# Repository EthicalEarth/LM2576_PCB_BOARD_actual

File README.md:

# LM2576_PCB_BOARD_actual
Good step-down converter. Project have stable status and released. After build, this board works perfectly from 2016-2021
Requires more space for radiators, but works great with forced ventilation.

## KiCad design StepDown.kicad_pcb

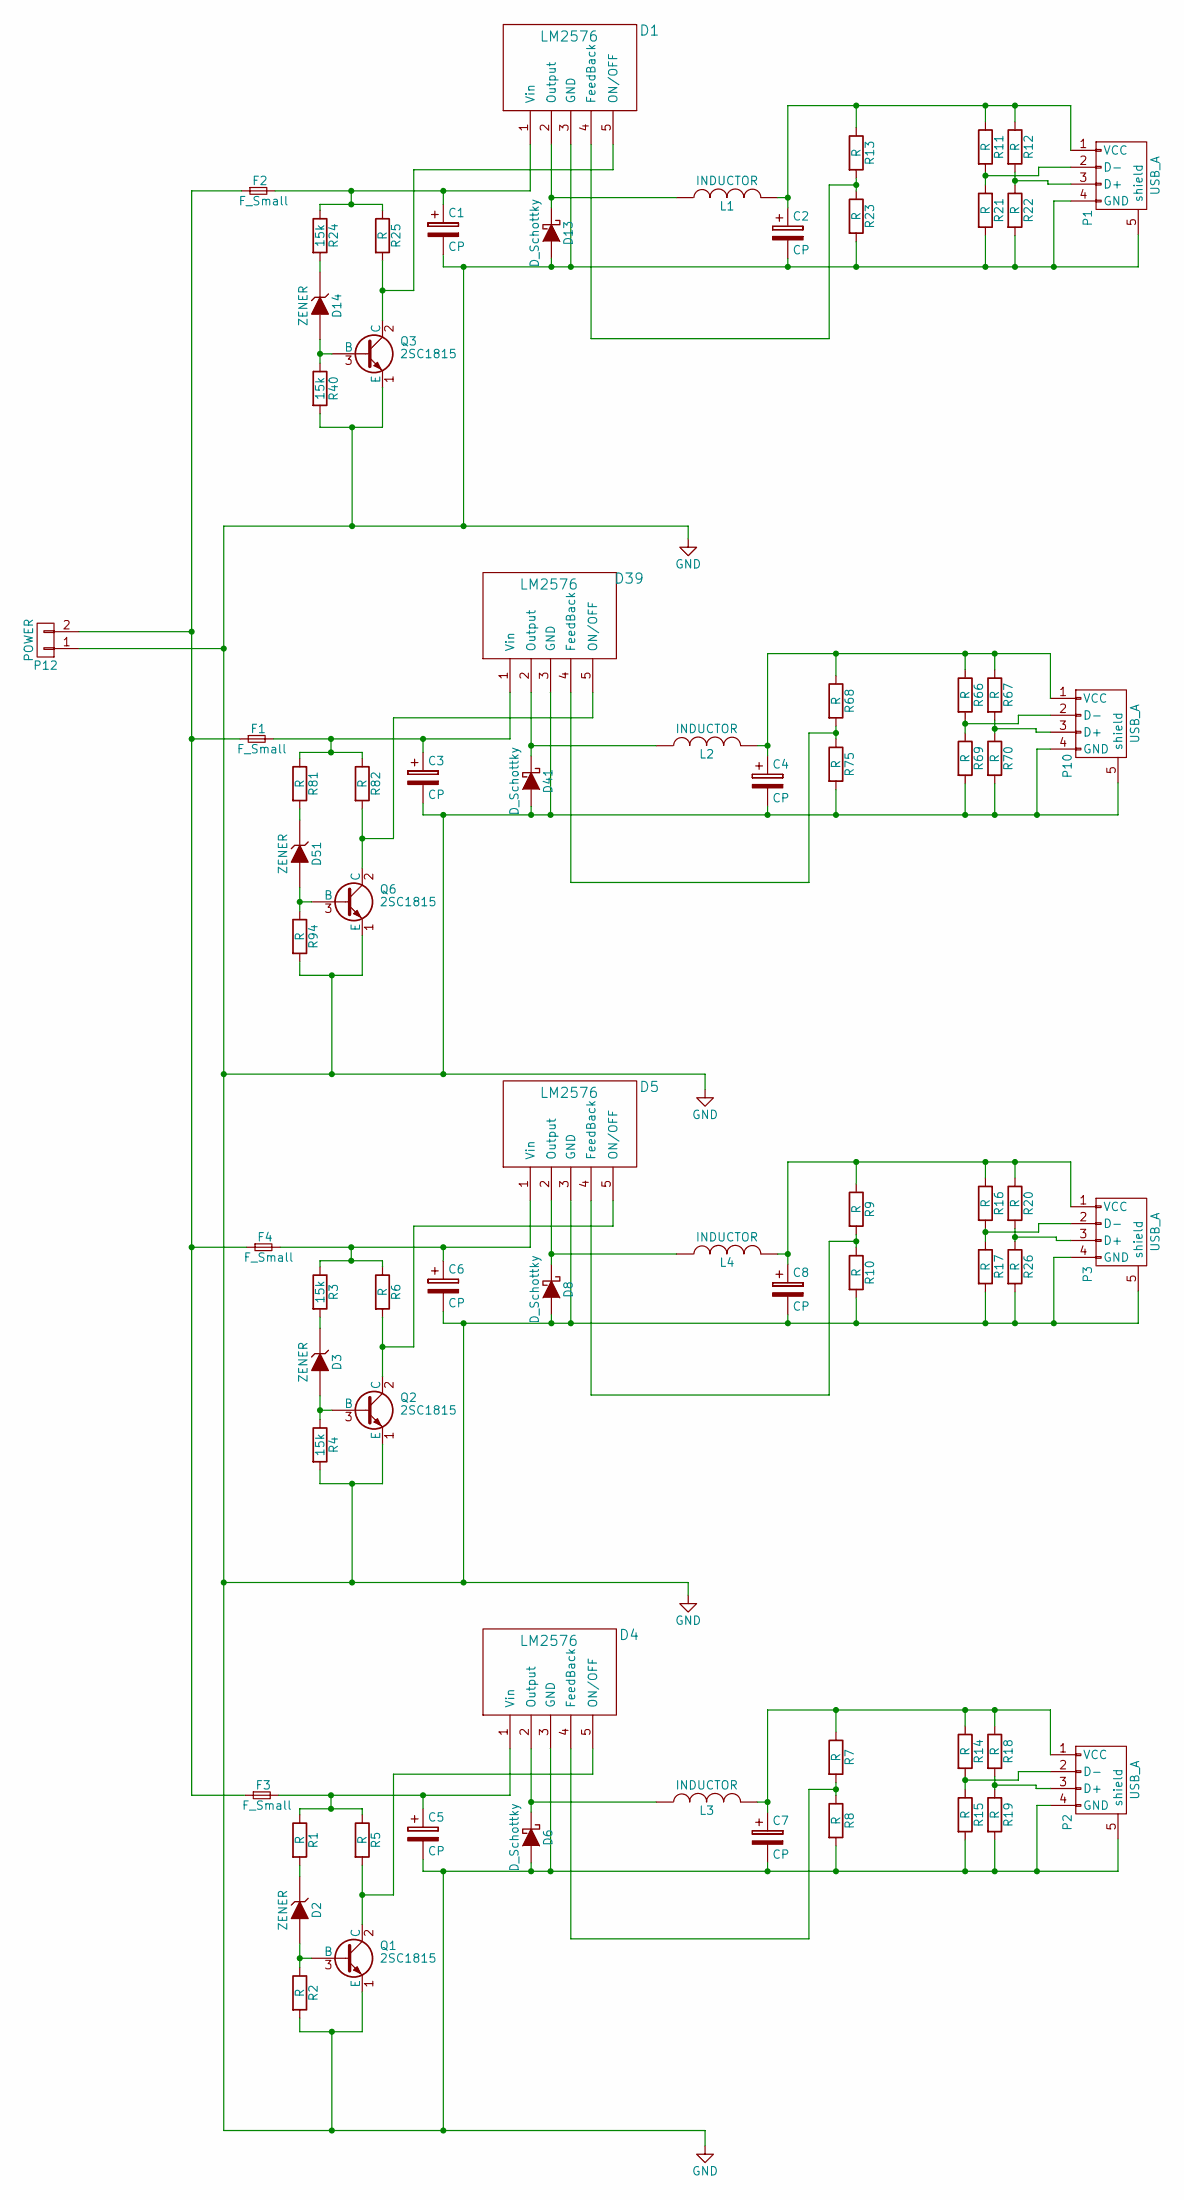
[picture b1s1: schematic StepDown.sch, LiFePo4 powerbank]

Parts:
C1, C2, C3, C4, C5, C6, C7, C8: CP; CP_Radial_D10.0mm_P5.00mm
D1, D4, D5, D39: LM2576; TO-220-5_Pentawatt_Multiwatt-5_Vertical_StaggeredType1
D2, D3, D14, D51: ZENER; D_DO-35_SOD27_P10.16mm_Horizontal
D6, D8, D13, D41: D_Schottky; D_DO-201AD_P15.24mm_Horizontal
F1, F2, F3, F4: F_Small; Fuseholder5x20_horiz_open_inline_Type-I
L1, L2, L3, L4: INDUCTOR; Choke_Toroid_8x16mm_Vertical
P1, P2, P3, P10: USB_A
P12: POWER; bornier2
Q1, Q2, Q3, Q6: 2SC1815; TO-92_Molded_Wide_Oval_Reverse
R1, R2, R5, R6, R7, R8, R9, R10, R11, R12, R13, R14, R15, R16, R17, R18, R19, R20, R21, R22, R23, R25, R26, R66, R67, R68, R69, R70, R75, R81, R82, R94: R; R_1206_HandSoldering
R3, R4, R24, R40: 15k; R_1206_HandSoldering

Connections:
GND: C1.2, C2.2, C3.2, C4.2, C5.2, C6.2, C7.2, C8.2, D1.3 (GND), D4.3 (GND), D5.3 (GND), D6.2 (A), D8.2 (A), D13.2 (A), D39.3 (GND), D41.2 (A), P1.4 (GND), P1.5 (shield), P2.4 (GND), P2.5 (shield), P3.4 (GND), P3.5 (shield), P10.4 (GND), P10.5 (shield), P12.1, Q1.1 (E), Q2.1 (E), Q3.1 (E), Q6.1 (E), R2.2, R4.2, R8.2, R10.2, R15.2, R17.2, R19.2, R21.2, R22.2, R23.2, R26.2, R40.2, R69.2, R70.2, R75.2, R94.2
unnamed: C1.1, D1.1 (Vin), F2.2, R24.1, R25.1
unnamed: C2.1, L1.2, P1.1 (VCC), R11.1, R12.1, R13.1
unnamed: C3.1, D39.1 (Vin), F1.2, R81.1, R82.1
unnamed: C4.1, L2.2, P10.1 (VCC), R66.1, R67.1, R68.1
unnamed: C5.1, D4.1 (Vin), F3.2, R1.1, R5.1
unnamed: C6.1, D5.1 (Vin), F4.2, R3.1, R6.1
unnamed: C7.1, L3.2, P2.1 (VCC), R7.1, R14.1, R18.1
unnamed: C8.1, L4.2, P3.1 (VCC), R9.1, R16.1, R20.1
unnamed: D1.2 (Output), D13.1 (K), L1.1
unnamed: D1.4 (FeedBack), R13.2, R23.1
unnamed: D1.5 (ON/OFF), Q3.2 (C), R25.2
unnamed: D2.1 (K), R1.2
unnamed: D2.2 (A), Q1.3 (B), R2.1
unnamed: D3.1 (K), R3.2
unnamed: D3.2 (A), Q2.3 (B), R4.1
unnamed: D4.2 (Output), D6.1 (K), L3.1
unnamed: D4.4 (FeedBack), R7.2, R8.1
unnamed: D4.5 (ON/OFF), Q1.2 (C), R5.2
unnamed: D5.2 (Output), D8.1 (K), L4.1
unnamed: D5.4 (FeedBack), R9.2, R10.1
unnamed: D5.5 (ON/OFF), Q2.2 (C), R6.2
unnamed: D14.1 (K), R24.2
unnamed: D14.2 (A), Q3.3 (B), R40.1
unnamed: D39.2 (Output), D41.1 (K), L2.1
unnamed: D39.4 (FeedBack), R68.2, R75.1
unnamed: D39.5 (ON/OFF), Q6.2 (C), R82.2
unnamed: D51.1 (K), R81.2
unnamed: D51.2 (A), Q6.3 (B), R94.1
unnamed: F1.1, F2.1, F3.1, F4.1, P12.2
unnamed: P1.2 (D-), R11.2, R21.1
unnamed: P1.3 (D+), R12.2, R22.1
unnamed: P2.2 (D-), R14.2, R15.1
unnamed: P2.3 (D+), R18.2, R19.1
unnamed: P3.2 (D-), R16.2, R17.1
unnamed: P3.3 (D+), R20.2, R26.1
unnamed: P10.2 (D-), R66.2, R69.1
unnamed: P10.3 (D+), R67.2, R70.1

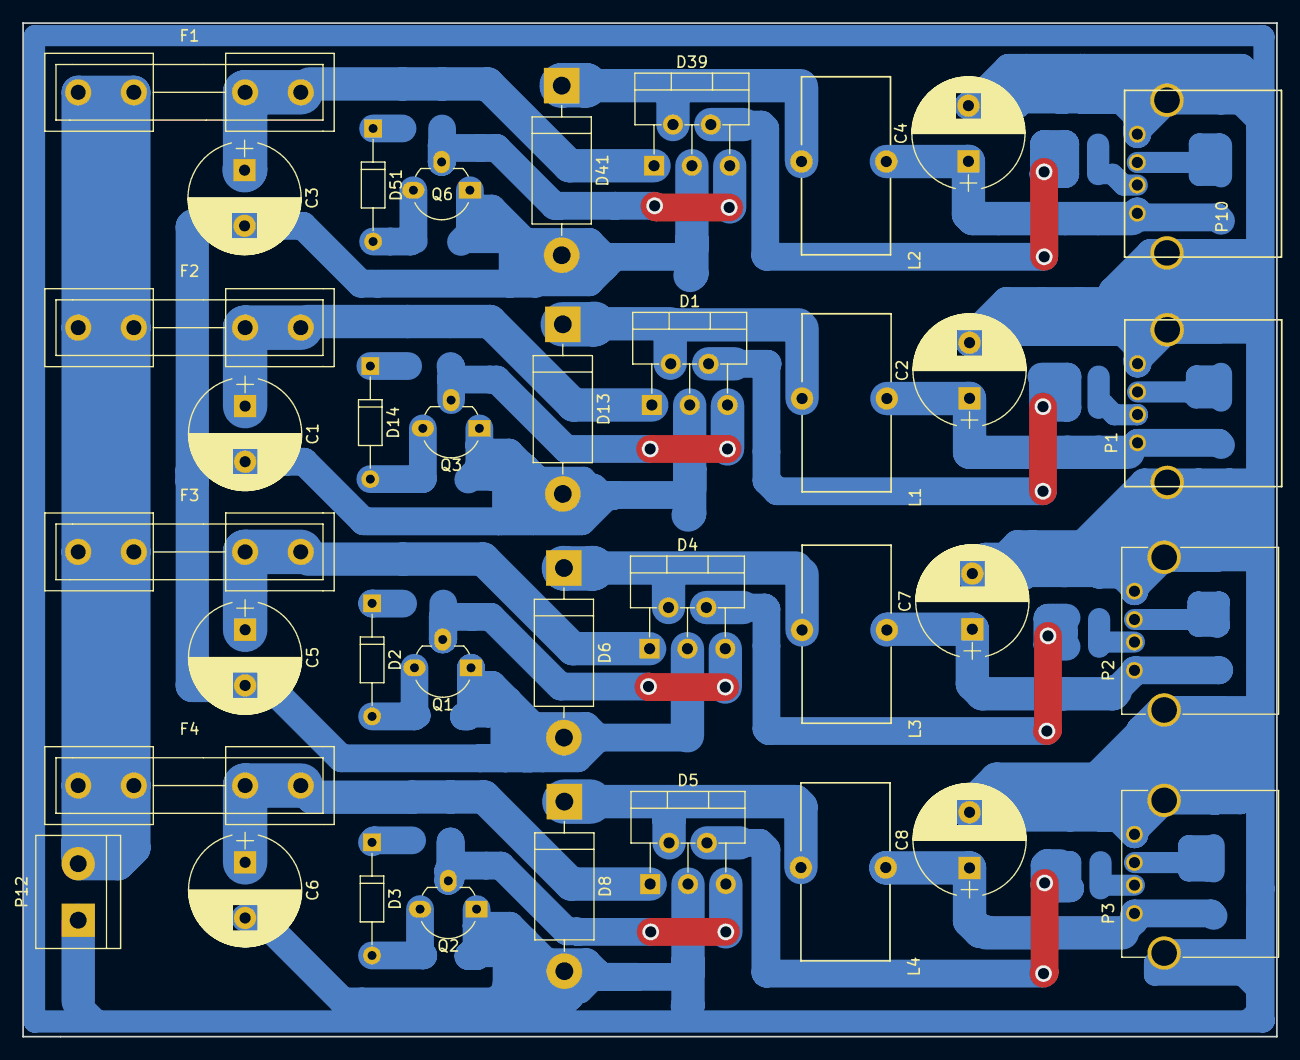
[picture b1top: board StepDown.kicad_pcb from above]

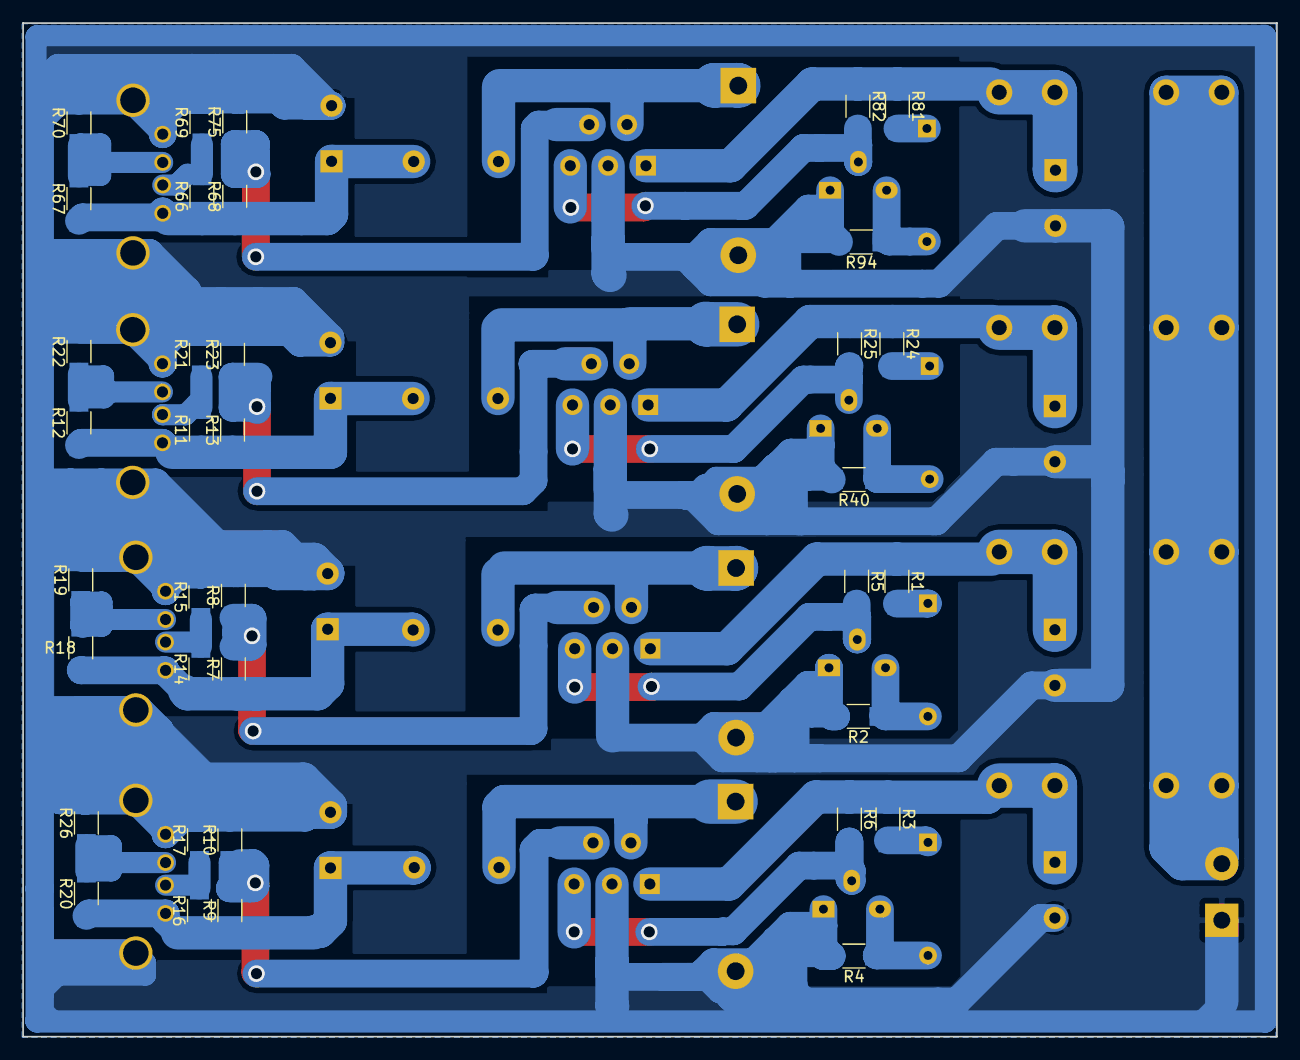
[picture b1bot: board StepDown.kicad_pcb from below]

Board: 2 copper layers, 112.7 x 91.1 mm, 73 parts (36 on the bottom side), 38 nets.

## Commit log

2018-07-28 Init
